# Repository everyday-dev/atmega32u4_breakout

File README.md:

# We've moved. 
In an effort to truly own and be in full control of our clients and personal information, source code, and documentation we've moved to a self-hosted Git server. You can find this project here: [git.everydaydev.io](https://git.everydaydev.io/opensource/atmega32u4_breakout)

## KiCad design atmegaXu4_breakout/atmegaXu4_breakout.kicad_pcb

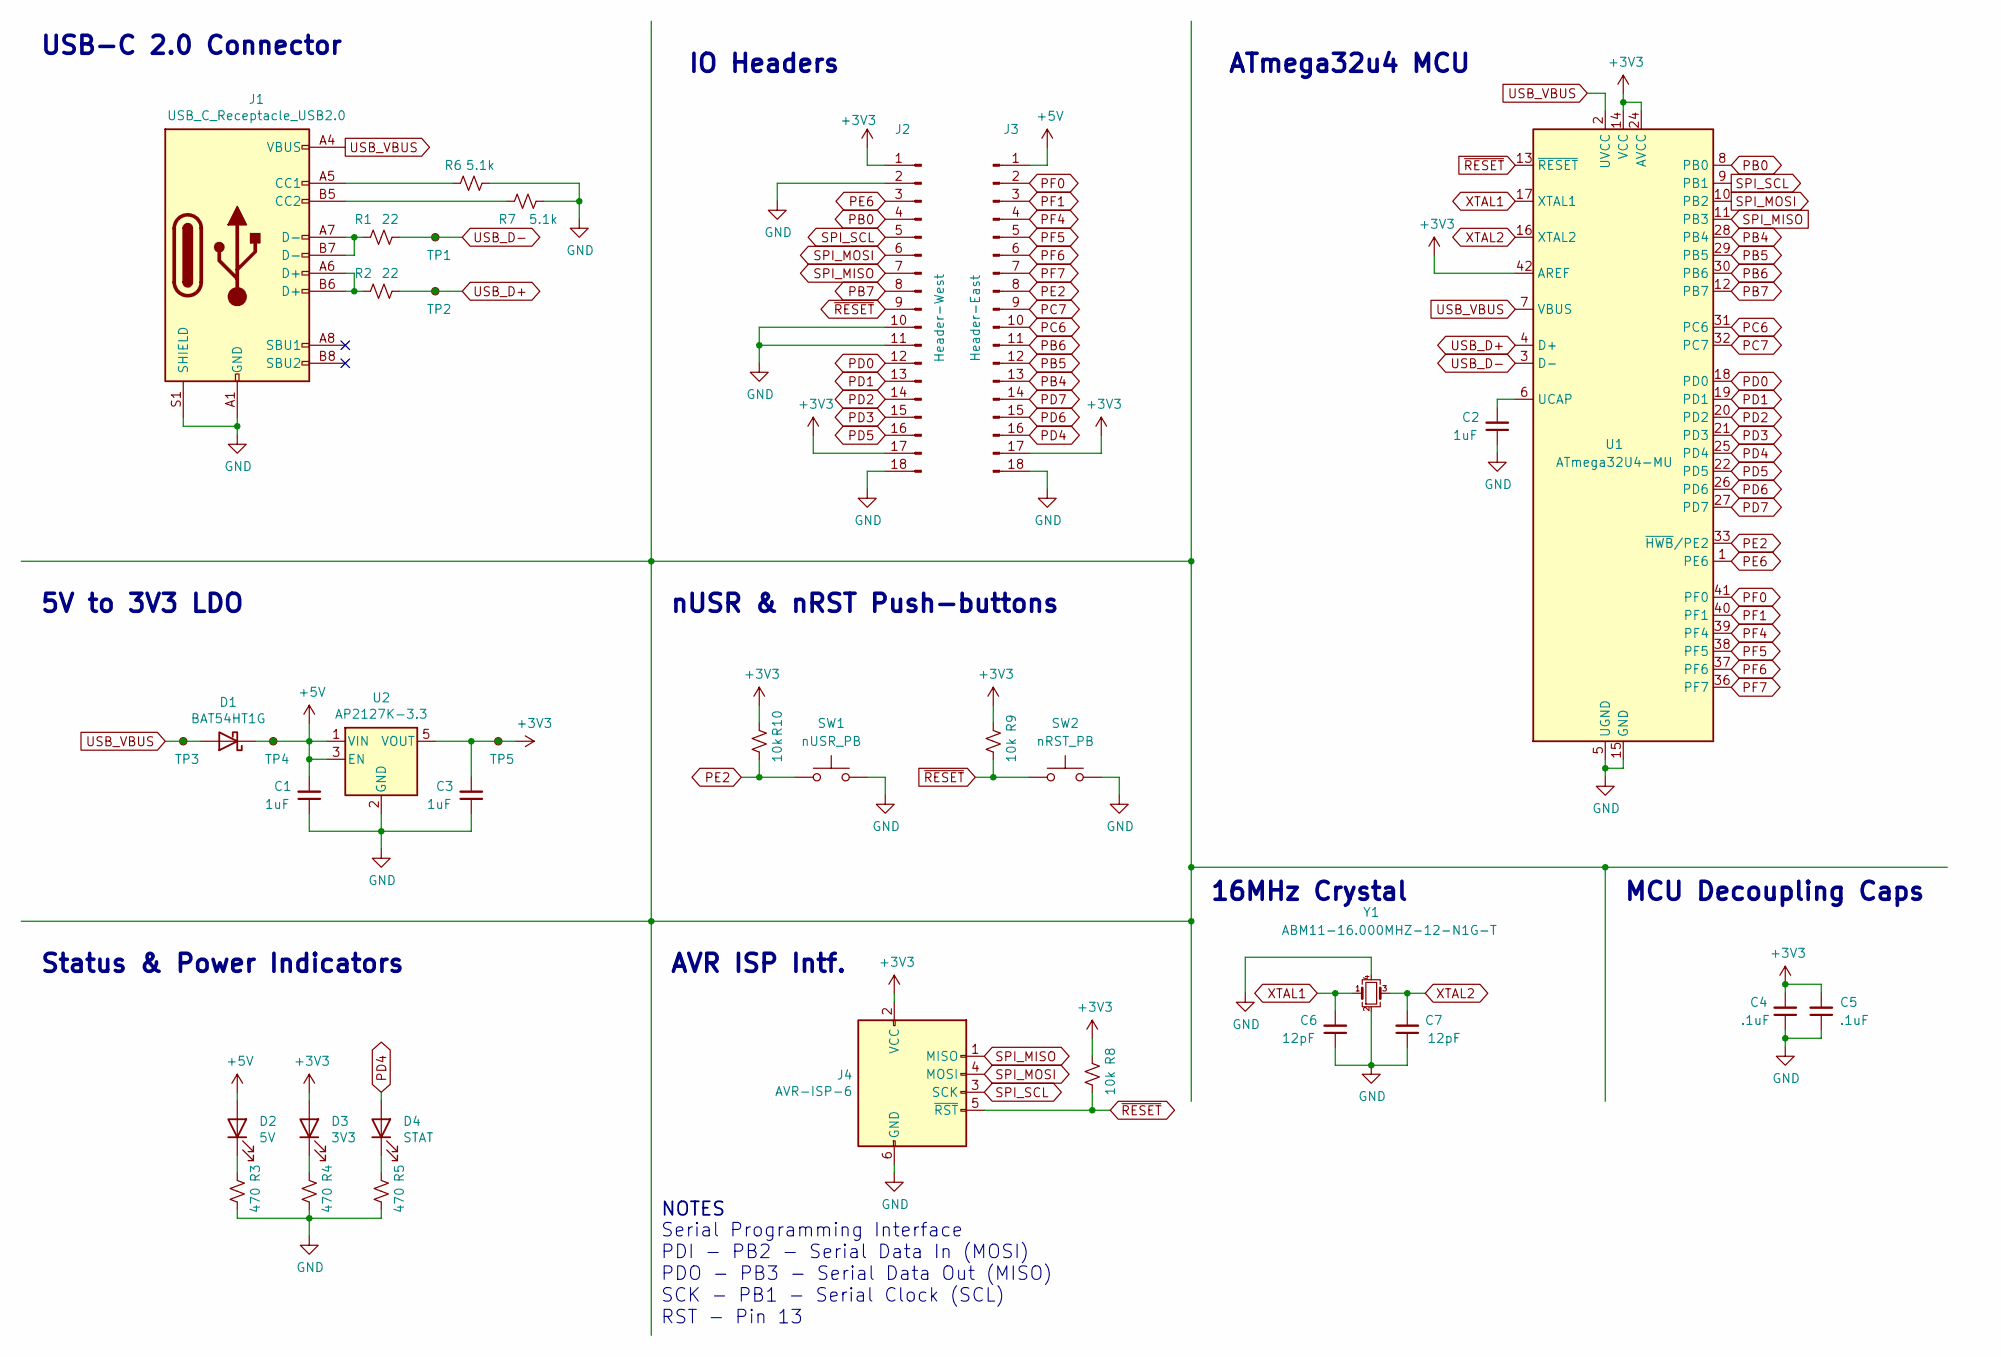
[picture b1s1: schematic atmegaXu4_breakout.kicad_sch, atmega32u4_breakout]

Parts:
C1, C2, C3: 1uF; C_0402_1005Metric
C4, C5: .1uF; C_0402_1005Metric
C6, C7: 12pF; C_0402_1005Metric
D1: BAT54HT1G; D_SOD-323
D2: 5V; LED_0603_1608Metric
D3: 3V3; LED_0603_1608Metric
D4: STAT; LED_0603_1608Metric
J1: USB_C_Receptacle_USB2.0; USB_C_Receptacle_GCT_USB4085; MPN USB4085
J2: Header-West; PinHeader_1x18_P2.54mm_Vertical
J3: Header-East; PinHeader_1x18_P2.54mm_Vertical
J4: AVR-ISP-6; PinHeader_2x03_P2.54mm_Vertical
R1, R2: 22; R_0402_1005Metric
R3, R4, R5: 470; R_0402_1005Metric
R6, R7: 5.1k; R_0402_1005Metric
R8, R9, R10: 10k; R_0402_1005Metric
SW1: nUSR_PB; SW_Push_1P1T_NO_CK_KMR2
SW2: nRST_PB; SW_Push_1P1T_NO_CK_KMR2
TP1, TP2: TestPoint_Small; TestPoint_Pad_1.0x1.0mm
TP3, TP4, TP5: TestPoint_Small; TestPoint_THTPad_1.0x1.0mm_Drill0.5mm
U1: ATmega32U4-MU; QFN-44-1EP_7x7mm_P0.5mm_EP5.2x5.2mm
U2: AP2127K-3.3; SOT-23-5
Y1: ABM11-16.000MHZ-12-N1G-T; Crystal_SMD_2016-4Pin_2.0x1.6mm

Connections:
+3V3: C3.2, C4.2, C5.2, D3.2 (A), J2.1, J2.17, J3.17, J4.2 (VCC), R8.2, R9.2, R10.2, TP5.1, U1.14 (VCC), U1.24 (AVCC), U1.34 (VCC), U1.42 (AREF), U1.44 (AVCC), U2.5 (VOUT)
+5V: C1.2, D1.1 (K), D2.2 (A), J3.1, TP4.1, U2.1 (VIN), U2.3 (EN)
GND: C1.1, C2.1, C3.1, C4.1, C5.1, C6.1, C7.1, J1.A1 (GND), J1.A12 (GND), J1.B1 (GND), J1.B12 (GND), J1.S1 (SHIELD), J2.2, J2.10, J2.11, J2.18, J3.18, J4.6 (GND), R3.1, R4.1, R5.1, R6.1, R7.1, SW1.2, SW2.2, U1.5 (UGND), U1.15 (GND), U1.23 (GND), U1.35 (GND), U1.43 (GND), U1.45 (GND), U2.2 (GND), Y1.2, Y1.4
unnamed: D2.1 (K), R3.2
unnamed: D3.1 (K), R4.2
unnamed: D4.1 (K), R5.2
unnamed: J1.A5 (CC1), R6.2
unnamed: J1.B5 (CC2), R7.2
unnamed: J1.A6 (D+), J1.B6 (D+), R2.2
unnamed: J1.A7 (D-), J1.B7 (D-), R1.2
unnamed: C2.2, U1.6 (UCAP)
PB0: J2.4, U1.8 (PB0)
PB4: J3.13, U1.28 (PB4)
PB5: J3.12, U1.29 (PB5)
PB6: J3.11, U1.30 (PB6)
PB7: J2.8, U1.12 (PB7)
PC6: J3.10, U1.31 (PC6)
PC7: J3.9, U1.32 (PC7)
PD0: J2.12, U1.18 (PD0)
PD1: J2.13, U1.19 (PD1)
PD2: J2.14, U1.20 (PD2)
PD3: J2.15, U1.21 (PD3)
PD4: D4.2 (A), J3.16, U1.25 (PD4)
PD5: J2.16, U1.22 (PD5)
PD6: J3.15, U1.26 (PD6)
PD7: J3.14, U1.27 (PD7)
PE2: J3.8, R10.1, SW1.1, U1.33 (~HWB/PE2)
PE6: J2.3, U1.1 (PE6)
PF0: J3.2, U1.41 (PF0)
PF1: J3.3, U1.40 (PF1)
PF4: J3.4, U1.39 (PF4)
PF5: J3.5, U1.38 (PF5)
PF6: J3.6, U1.37 (PF6)
PF7: J3.7, U1.36 (PF7)
SPI_MISO: J2.7, J4.1 (MISO), U1.11 (PB3)
SPI_MOSI: J2.6, J4.4 (MOSI), U1.10 (PB2)
SPI_SCL: J2.5, J4.3 (SCK), U1.9 (PB1)
USB_D+: R2.1, TP2.1, U1.4 (D+)
USB_D-: R1.1, TP1.1, U1.3 (D-)
USB_VBUS: D1.2 (A), J1.A4 (VBUS), J1.A9 (VBUS), J1.B4 (VBUS), J1.B9 (VBUS), TP3.1, U1.2 (UVCC), U1.7 (VBUS)
XTAL1: C6.2, U1.17 (XTAL1), Y1.1
XTAL2: C7.2, U1.16 (XTAL2), Y1.3
~RESET: J2.9, J4.5 (~RST), R8.1, R9.1, SW2.1, U1.13 (~RESET)

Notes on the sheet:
nUSR & nRST Push-buttons
IO Headers
5V to 3V3 LDO
16MHz Crystal
AVR ISP Intf.
MCU Decoupling Caps
NOTES
Serial Programming Interface PDI - PB2 - Serial Data In (MOSI) PDO - PB3 - Serial Data Out (MISO) SCK - PB1 - Serial Clock (SCL) RST - Pin 13
USB-C 2.0 Connector
Status & Power Indicators
ATmega32u4 MCU

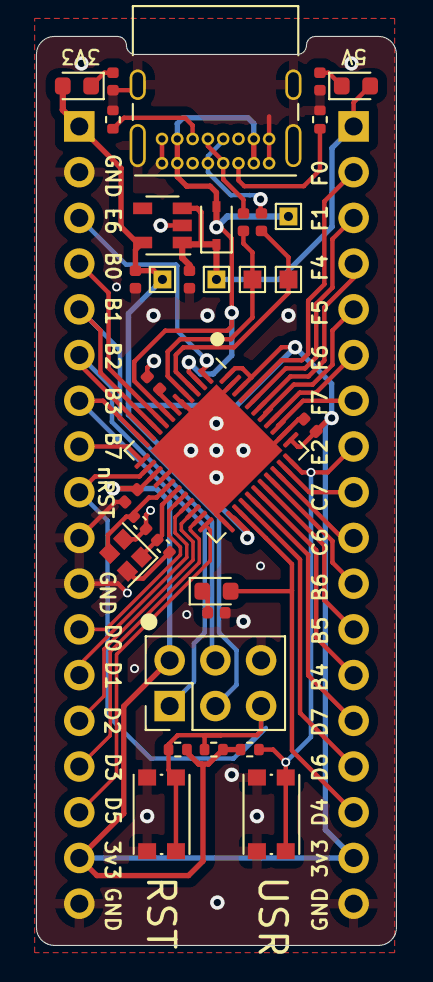
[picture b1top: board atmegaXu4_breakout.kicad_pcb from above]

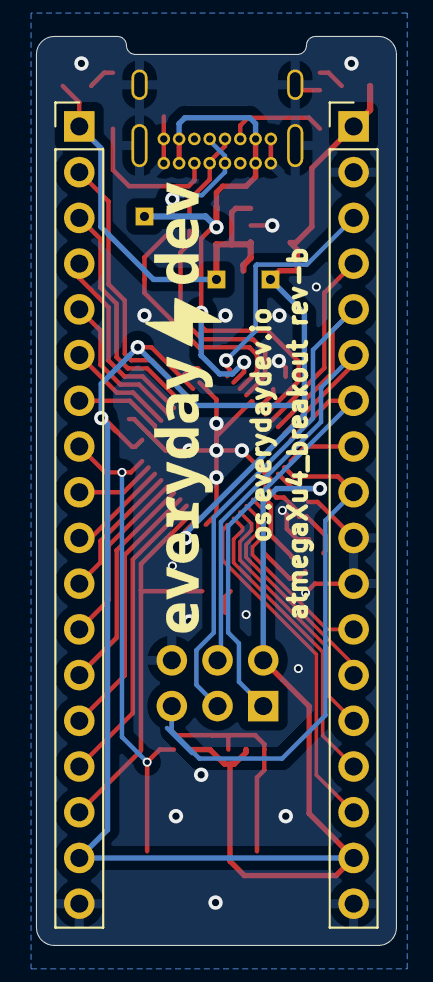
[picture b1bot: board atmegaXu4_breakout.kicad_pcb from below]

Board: 2 copper layers, 20.0 x 50.5 mm, 35 parts (2 on the bottom side), 43 nets.

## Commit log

2020-08-19 Adding first rev of the atmegaXu4 breakout board
2020-08-25 Adding an image of the board and a README
2022-12-22 Fixed missing 5.1k CC pins and cleaned up routing
2022-12-22 Cleaned up the README
2022-12-22 Fixing broken docs link
2022-12-22 Final DRC before release
2022-12-22 Removing commited backups
2022-12-22 Removing unused kicad_mod for the logo
2022-12-27 Added on-board 16MHz crystal
2022-12-27 Deleting the .kicad_prl file since it's dev machine specific
2022-12-27 Releaseing RevB
2022-12-27 Only ignore .step files when they are not in the models/ folder
2023-02-06 Added nRST and nUSR push-buttons
2023-02-07 Added CI utils for automating releases
2023-02-07 Started adding MFP values for components
2023-04-07 Clean DRC.
2023-04-07 Fixing breadboard-io reference in CI file
2023-06-26 Updated BOM script and CI yml files
2023-06-26 Updated silk logo to everydaydev
2023-10-10 Update logo in silkscreen to full everydaydev logo
